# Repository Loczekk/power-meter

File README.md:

# Power-meter
First fully working version with some mistakes. Callibrated and tested with 3GHz, 6us pulses in power range between -35 dBm up to -15 dBm.

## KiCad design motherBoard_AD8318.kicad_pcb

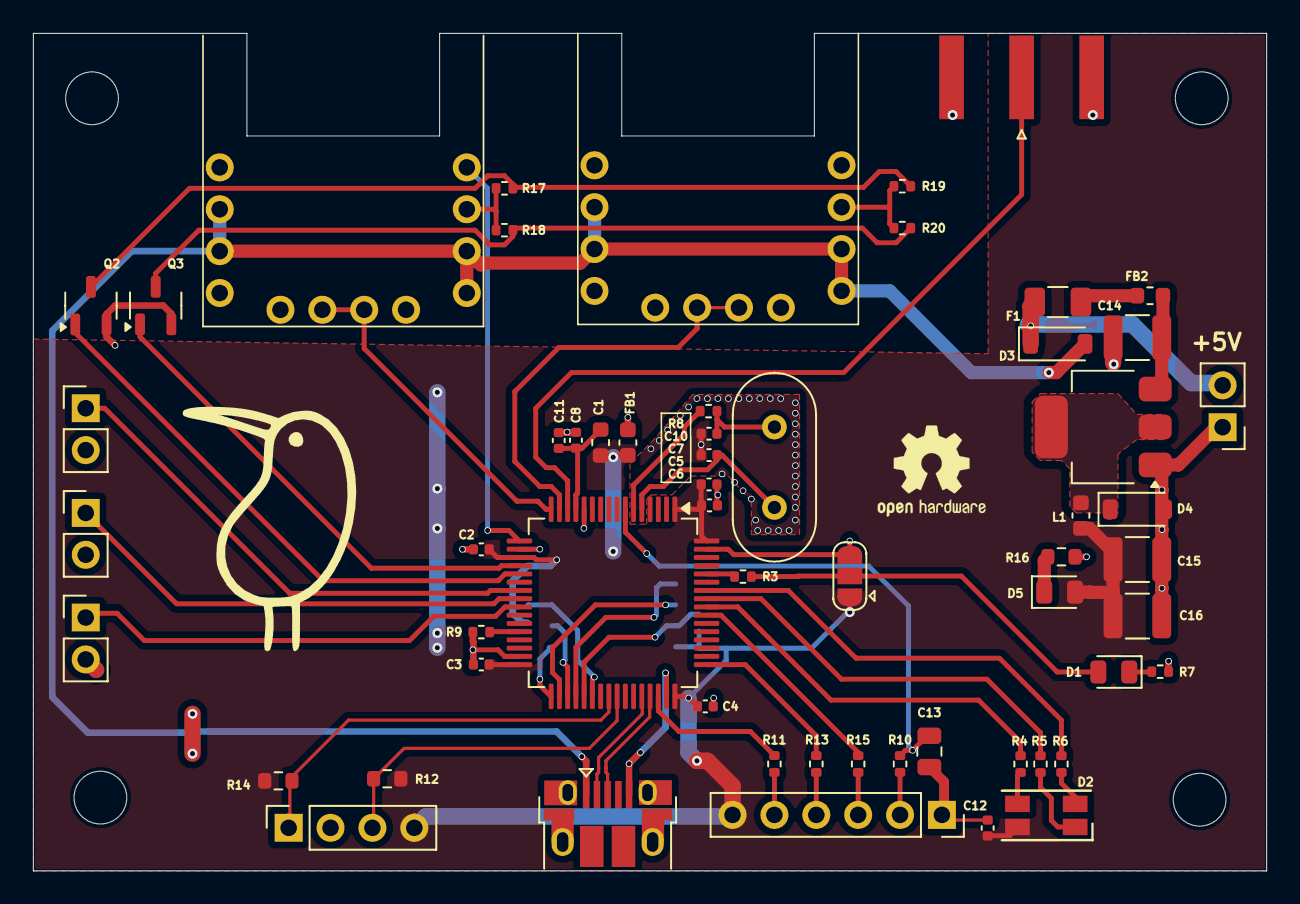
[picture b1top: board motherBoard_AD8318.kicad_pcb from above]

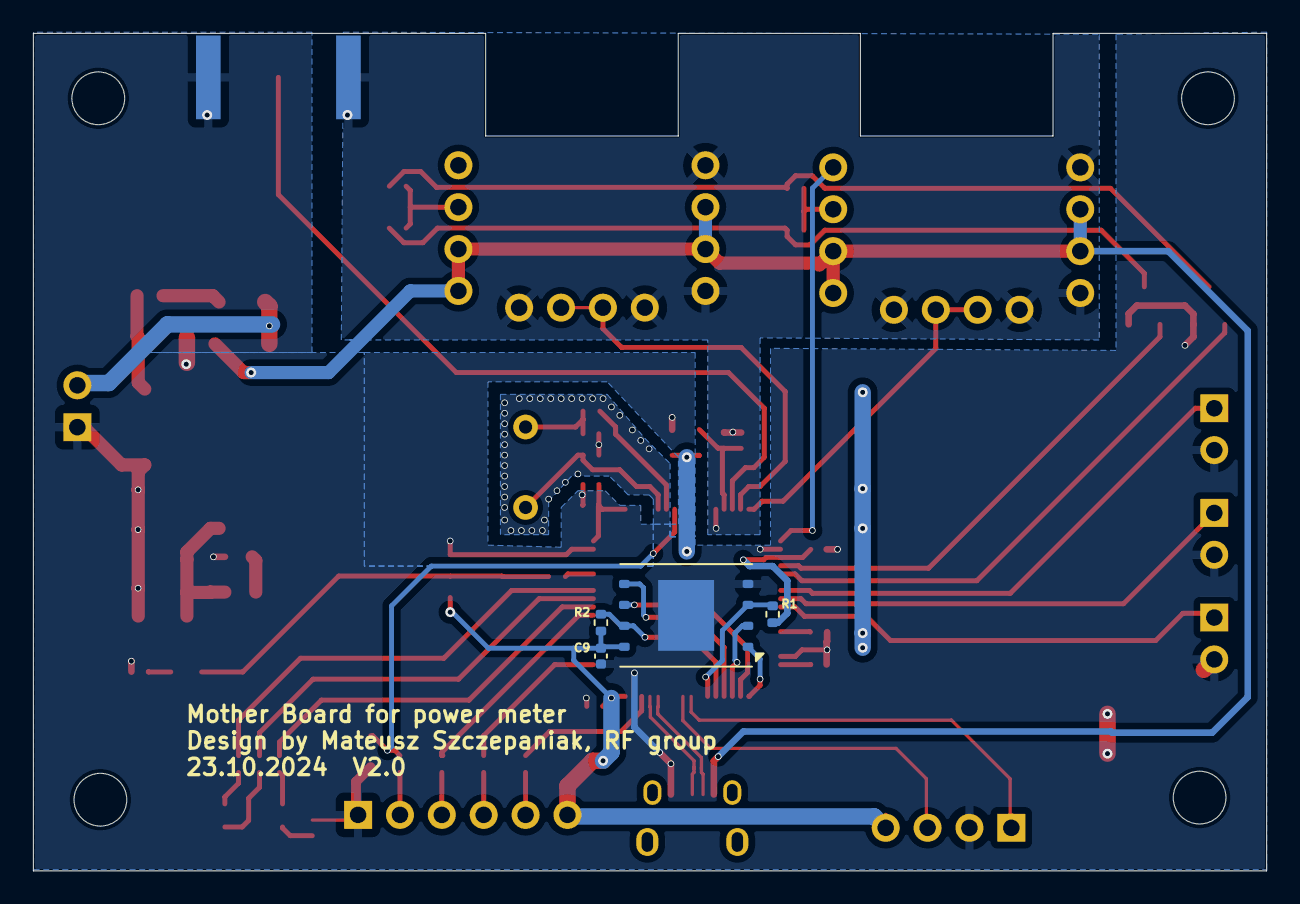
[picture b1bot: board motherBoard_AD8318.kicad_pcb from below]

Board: 2 copper layers, 74.8 x 50.8 mm, 65 parts (4 on the bottom side), 53 nets.

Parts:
C1: 4u7; C_0603_1608Metric
C2, C3, C4, C5, C6, C9, C11, C12: 100n; C_0402_1005Metric
C7, C10: 12p; C_0402_1005Metric
C8: 1u; C_0402_1005Metric
C13: 100n; C_0805_2012Metric
C14, C15, C16: 10u; C_1210_3225Metric
D1: LED_0805_2012Metric
D2: LED_RGB_1210
D3, D4: B5819W; D_SOD-123
D5: GREEN; LED_0805_2012Metric
F1: 250mA; Fuse_1206_3216Metric
FB1: 600MHz; L_0603_1608Metric
FB2: 600 @ 600 MHz; L_0603_1608Metric
H1, H2, H3, H4: MountingHole; MountingHole_3.2mm_M3
J1: SWDIO; PinSocket_1x06_P2.54mm_Vertical
J2: USB_Micro-B_Amphenol_10103594-0001LF_Horizontal
J3: wyswietlacz; PinSocket_1x04_P2.54mm_Vertical
J201: power; PinHeader_1x02_P2.54mm_Vertical
L1: 10u; C_0603_1608Metric
Q2, Q3: BSS138; SOT-23-3
R1, R2, R3, R9: 10k; R_0402_1005Metric
R4, R5, R6, R7, R17, R19: 1k; R_0402_1005Metric
R8: 47; R_0402_1005Metric
R10, R11, R13, R15: 22; R_0402_1005Metric
R12, R14: 2k2; R_0603_1608Metric
R16: 1k5; R_0603_1608Metric
R18, R20: 510R; R_0402_1005Metric
SW1: SolderJumper-3_P1.3mm_Open_RoundedPad1.0x1.5mm
SW2, SW3, SW4: SW_Push; PinHeader_1x02_P2.54mm_Vertical
U1: flash; WSON-8-1EP_8x6mm_P1.27mm_EP3.4x4.3mm
U2: STM32F446RCTx; LQFP-64_10x10mm_P0.5mm
U3: AMS1117-3.3; SOT-223-3_TabPin2
U4, U5: detektor_AD8318
Y1: 16MHz; Crystal_HC49-4H_Vertical

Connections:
1k: Q2.1 (G), U2.21 (PA5)
500R: Q3.1 (G), U2.20 (PA4)
+3.3V: C1.1, C2.1, C3.1, C4.1, C5.1, C6.1, C9.1, C12.1, C15.1, C16.1, D2.4 (A), D5.2 (A), FB1.2, J1.6, J3.4 (Pin_1), L1.2, R1.1, R2.1, R12.1, R14.1, SW1.1 (A), U1.8 (VCC), U2.1 (VBAT), U2.19 (VDD), U2.32 (VDD), U2.48 (VDD), U2.64 (VDD)
+3.3VA: C8.1, C11.1, FB1.1, U2.13 (VDDA)
+5V: D3.2 (A), J2.1 (VBUS), U4.2 (5V), U4.3 (5V), U4.9 (5V), U4.10 (5V), U5.2 (5V), U5.3 (5V), U5.9 (5V), U5.10 (5V)
ADC1_IN0_DET1: U2.16 (PA2), U4.6 (WY), U4.7 (WY)
ADC2_IN1_DET2: U2.15 (PA1), U5.6 (WY), U5.7 (WY)
ADC3_IN3_TEMP: U2.17 (PA3), U4.12 (TEMP)
BOOT0: R3.2, U2.60 (BOOT0)
BOOT1: R9.1, U2.28 (PB2)
Button1: SW2.1, U2.23 (PA7)
Button2: SW3.1, U2.24 (PC4)
Button3: SW4.1, U2.25 (PC5)
FLASH_!HOLD: R2.2, U1.7 (~HOLD), U2.37 (PC6)
FLASH_!WP: R1.2, U1.3 (~WP), U2.38 (PC7)
GND: C1.2, C2.2, C3.2, C4.2, C5.2, C6.2, C7.2, C9.2, C10.2, C12.2, C13.2, C14.2, C15.2, C16.2, D4.2 (A), J1.1, J2.5 (GND), J3.2 (Pin_4), J201.1, Q2.2 (S), Q3.2 (S), R7.1, R9.2, R16.2, SW1.3 (C), SW2.2, SW3.2, SW4.2, U1.4 (GND), U1.9 (EP), U2.18 (VSS), U2.31 (VSS), U2.47 (VSS), U2.63 (VSS), U3.1 (GND)
GNDA: C8.2, C11.2, U2.12 (VSSA), U4.1 (GND), U4.4 (GND), U4.5 (GND), U4.8 (GND), U5.1 (GND), U5.4 (GND), U5.5 (GND), U5.8 (GND)
HSE_IN: C7.1, U2.5 (PH0), Y1.1
HSE_OUT: R8.1, U2.6 (PH1)
I2C1_SCL: J3.1 (Pin_2), R12.2, U2.41 (PA8)
I2C1_SDA: J3.3, R14.2, U2.40 (PC9)
NRST: C13.1, R10.1, U2.7 (NRST)
unnamed: C10.1, R8.2, Y1.2
unnamed: D1.2 (A), R3.1, SW1.2 (B)
unnamed: D1.1 (K), R7.2
unnamed: D2.3 (BK), R4.1
unnamed: D2.2 (GK), R6.1
unnamed: D2.1 (RK), R5.1
unnamed: D4.1 (K), L1.1, U3.2 (VO)
unnamed: D5.1 (K), R16.1
unnamed: F1.1, FB2.2
unnamed: J1.2, R10.2
unnamed: J1.3, R15.2
unnamed: J1.4, R13.2
unnamed: J1.5, R11.2
unnamed: Q2.3 (D), R17.2, R19.2
unnamed: Q3.3 (D), R18.2, R20.2
unnamed: C14.1, FB2.1, U3.3 (VI)
SPI2_!CS: U1.1 (~CS), U2.33 (PB12)
SPI2_MISO: U1.2 (DO(IO1)), U2.35 (PB14)
SPI2_MOSI: U1.5 (DI(IO0)), U2.36 (PB15)
SPI2_SCK: U1.6 (CLK), U2.34 (PB13)
SWCLK: R13.1, U2.49 (PA14)
SWDIO: R11.1, U2.46 (PA13)
SWO: R15.1, U2.55 (PB3)
TIM3_CH1: R4.2, U2.56 (PB4)
TIM3_CH2: R5.2, U2.57 (PB5)
TIM4_CH1: R6.2, U2.58 (PB6)
T_ADJ_1: R17.1, R18.1, U4.11 (T_ADJ)
T_ADJ_2: R19.1, R20.1, U5.11 (T_ADJ)
USB_D+: J2.3 (D+), U2.45 (PA12)
USB_D-: J2.2 (D-), U2.44 (PA11)
VCC: D3.1 (K), F1.2, J201.2

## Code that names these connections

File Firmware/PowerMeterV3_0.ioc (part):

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Mcu.Name=STM32F446R(C-E)Tx
Mcu.Package=LQFP64
Mcu.UserName=STM32F446RCTx
PA0-WKUP.GPIOParameters=GPIO_PuPd,GPIO_Label
PA0-WKUP.GPIO_Label=Comp_input
PA0-WKUP.GPIO_PuPd=GPIO_PULLDOWN
PA0-WKUP.Signal=GPXTI0
PA1.Signal=ADCx_IN1
PA13.Mode=Serial_Wire
PA13.Signal=SYS_JTMS-SWDIO
PA14.Mode=Serial_Wire
PA14.Signal=SYS_JTCK-SWCLK
PA2.Signal=ADCx_IN2
PA4.GPIOParameters=GPIO_PuPd,GPIO_Label
PA4.GPIO_Label=OHM500
PA4.GPIO_PuPd=GPIO_PULLUP
PA4.Signal=GPIO_Output
PA5.GPIOParameters=GPIO_PuPd,GPIO_Label
PA5.GPIO_Label=OHM51
PA5.GPIO_PuPd=GPIO_PULLUP
PA5.Signal=GPIO_Output
PA7.GPIOParameters=GPIO_Label
PA7.GPIO_Label=TEST
PA7.Signal=GPIO_Output
PA8.Mode=I2C
PA8.Signal=I2C3_SCL
PB4.GPIOParameters=GPIO_Label
PB4.GPIO_Label=LD2
PB4.Signal=GPIO_Output
PC9.Mode=I2C
PC9.Signal=I2C3_SDA
RCC.HSE_VALUE=16000000
RCC.SYSCLKFreq_VALUE=64000000
RCC.SYSCLKSource=RCC_SYSCLKSOURCE_PLLCLK
board=custom
